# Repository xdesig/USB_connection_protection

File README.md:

# USB connection protection  V 001

This circuit is responsible for the protection against excessive consumption by resettable fuse and protection against overvoltage. to protect each I / O pin from high voltages, from ESD for electronic equipment that can be connected via the USB bus.
Rugged diodes (TVS Diode Arrays (SPA® Diodes) littelfuse) can safely absorb repetitive strokes of ESD at the maximum level specified in the international standard IEC 61000-4-2 (Level 4, contact discharge of ± 8 kV) without performance degradation. Their very low load capacity also makes them ideal for protecting high speed signal pins such as HDMI, DVI, USB2.0 and IEEE 1394.

Protects both the computer and the peripheral. I designed this small circuit when an improper mount of a driver in a RAMPS, burned the USB of the Laptop :-(

Buy PCB in [PCBWAY]

Components: Electronics Lcsc

[USB Female]

[USB Male]

PTC Resettable fuse [SMD1206B050TF]

TVS Littelfuse [SP3003-02JTG]

![Render][RENDER]
![Real][Real]

## Author and license
* Author: [XDeSIG][TWI01]
* License: [Attribution-ShareAlike 4.0 International] [CCBY-SA4.0]

<!-- links -->

[CCBY-SA4.0]: http://creativecommons.org/licenses/by-sa/4.0/
[TWI01]: https://twitter.com/xdesig
[RENDER]: USB_Protect_A_34.png
[Real]: USB_Protect_A_Preta.jpg
[PCBWAY]: https://www.pcbway.com/project/shareproject/USB_connection_protection.html
[USB Female]: https://lcsc.com/product-detail/USB-Connectors_Jing-Extension-of-the-Electronic-Co-LCSC-USB-A-F900-14-1-Not-high-temperature_C2344.html
[USB Male]: https://lcsc.com/product-detail/USB-Connectors_Atype-USBMale-head-USB-05_C112454.html
[SMD1206B050TF]: https://lcsc.com/product-detail/Others_Brightking-Elec-TAIWAN-SMD1206B025TF_C269112.html
[SP3003-02JTG]: https://lcsc.com/product-detail/TVS_Littelfuse_SP3003-02JTG_SP3003-02JTG_C151302.html

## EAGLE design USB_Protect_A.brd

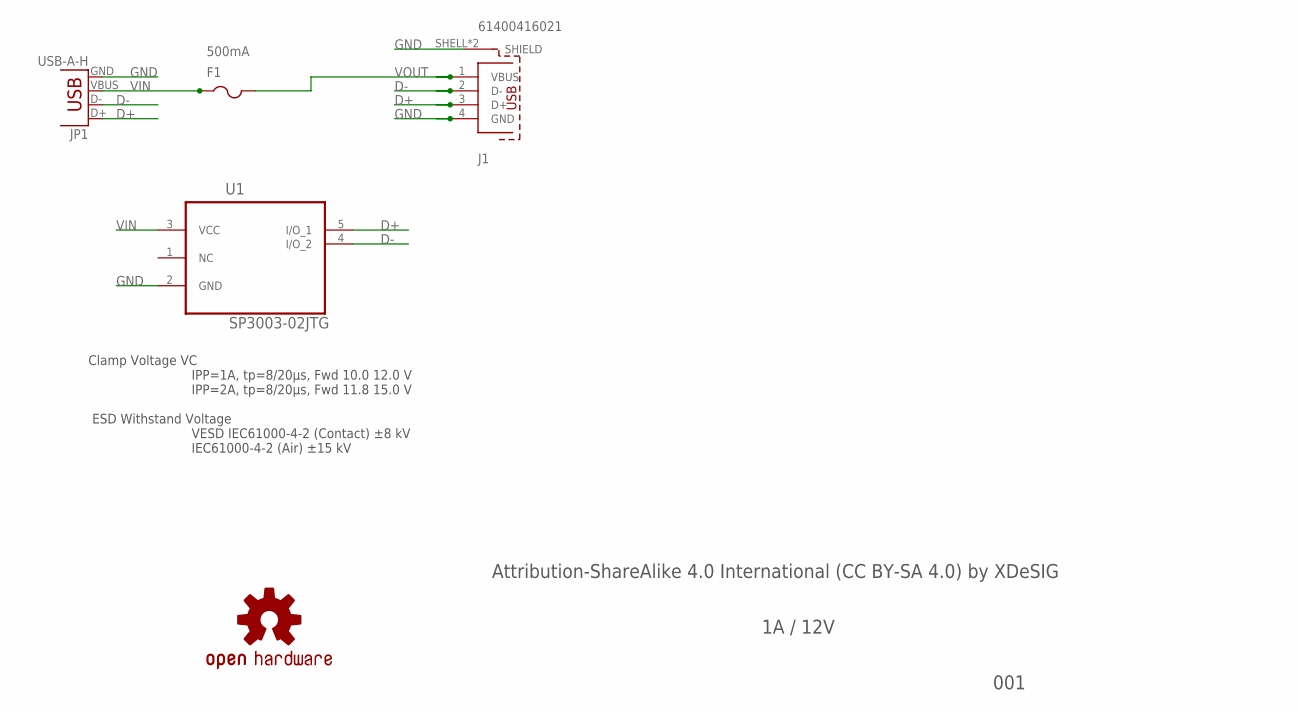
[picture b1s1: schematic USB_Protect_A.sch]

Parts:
F1: 500mA; R1206
J1: 61400416021
JP1: USB-A-H
LOGO1: OSHW-LOGOS; ESCORNA_LBRESCORNA_CPU_2_10_SPARKFUN-AESTHETICS_OSHW-LOGO-S
U1: SP3003-02JTG; SOT65P220X110-5N

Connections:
D+: J1.3 (D+), JP1.D+, U1.5 (I/O_1)
D-: J1.2 (D-), JP1.D-, U1.4 (I/O_2)
GND: J1.4 (GND), J1.SHELL (SHIELD), J1.SHELL1 (SHIELD), JP1.GND, U1.2 (GND)
VIN: F1.1, JP1.VBUS, U1.3 (VCC)
VOUT: F1.2, J1.1 (VBUS)

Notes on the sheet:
Clamp Voltage VC IPP=1A, tp=8/20µs, Fwd 10.0 12.0 V IPP=2A, tp=8/20µs, Fwd 11.8 15.0 V ESD Withstand Voltage VESD IEC61000-4-2 (Contact) ±8 kV IEC61000-4-2 (Air) ±15 kV
1A / 12V
Attribution-ShareAlike 4.0 International (CC BY-SA 4.0) by XDeSIG
001

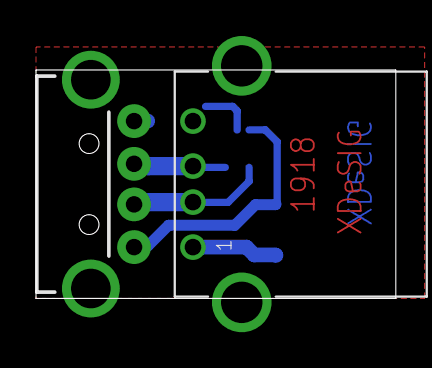
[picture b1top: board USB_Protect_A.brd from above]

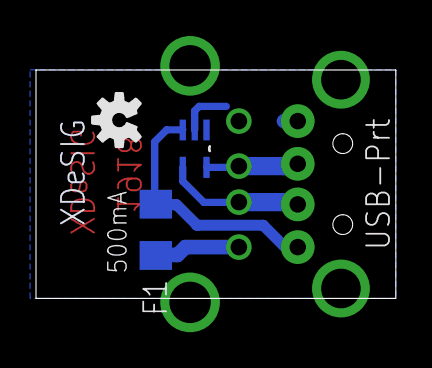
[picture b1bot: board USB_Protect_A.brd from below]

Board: 2 copper layers, 20.0 x 12.7 mm, 5 parts (3 on the bottom side), 5 nets.

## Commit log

2019-05-06 Inital commit
    Public
2019-05-06 Revert "Inital commit"
    This reverts commit 5c7089dacc69489dbe68ce8c657147b81196c9f3.
2019-05-06 Initial
    Initial commit
2019-06-01 Update Photo
2019-09-05 Update
    Update details
2025-03-07 User update

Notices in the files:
parts and their libraries:
SparkFun-Connectors: Licensing: Creative Commons ShareAlike 4.0 International - https://creativecommons.org/licenses/by-sa/4.0
